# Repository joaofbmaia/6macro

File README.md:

# 6macro
This is my first attempt at designing a keyboard. Is consists of a 6-key board intended for macros or as a dedicated controller for games with few bindings such as OSU.

RGB lighting is supported and the whole build is powered by an ATmega32U2 with the QMK firmware. The 6 switches are PCB-mounted.

The case is still a WIP and is built with stacked layers of laser-cut acrylic and a top layer of decorative aluminum.

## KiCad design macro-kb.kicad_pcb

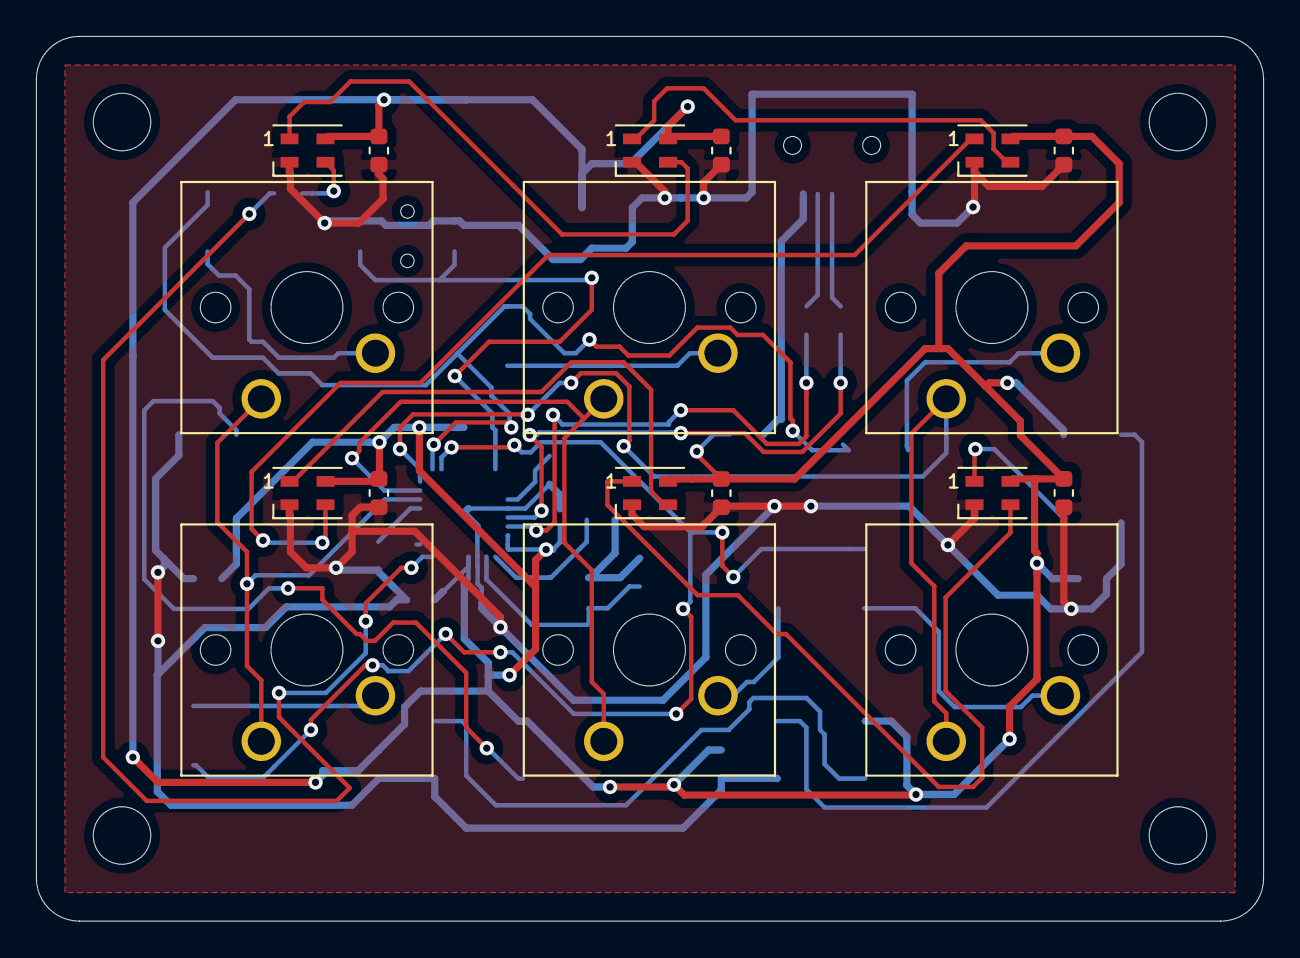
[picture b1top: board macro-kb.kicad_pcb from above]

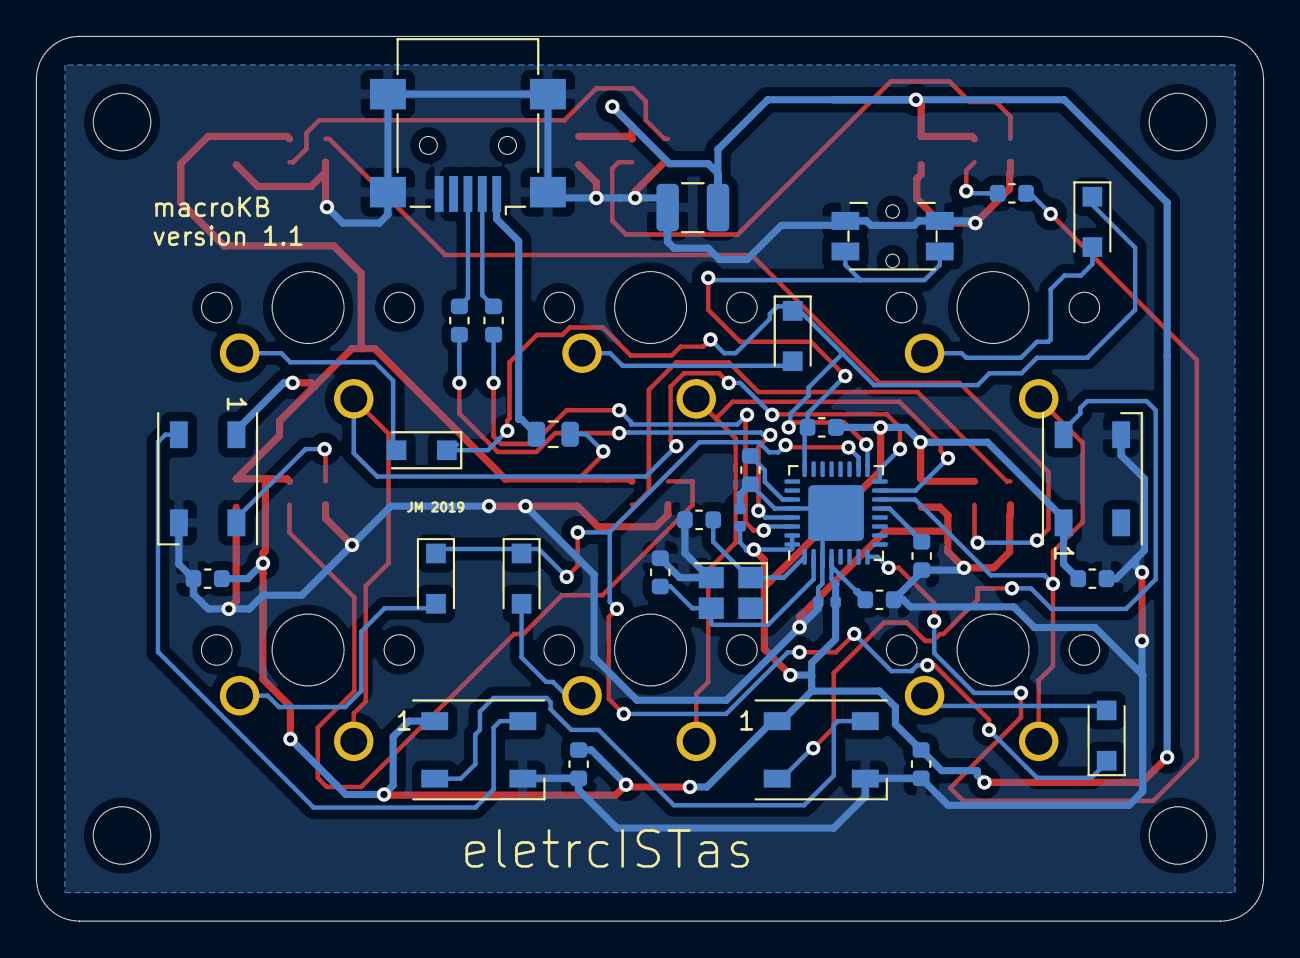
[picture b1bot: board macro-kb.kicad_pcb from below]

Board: 2 copper layers, 68.3 x 49.2 mm, 49 parts (31 on the bottom side), 34 nets.

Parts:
C1: 1uF; C_0603_1608Metric
C2, C3: 0.1uF; C_0402_1005Metric
C4: 10uF; C_0603_1608Metric
C5, C6: 22pF; C_0603_1608Metric
C7, C8, C9, C10, C11, C12, C13, C14, C15, C16: 0.1uF; C_0603_1608Metric
C17: 100uF; C_1210_3225Metric
D1, D2, D3, D4, D5, D6: SOD-123F; D_SOD-123F
D7, D8, D9, D10: WS2812B; LED_WS2812B_PLCC4_5.0x5.0mm_P3.2mm
D11, D12, D13, D14, D15, D16: SK6805; LED_SK6805_PLCC4_2.4x2.7mm_P1.3mm
F1: 500mA; Fuse_0805_2012Metric
MX1, MX2, MX3, MX4, MX5, MX6: MX-1U; SW_Cherry_MX_1.00u_PCB
R1, R4: 10K; R_0603_1608Metric
R2, R3: 22; R_0603_1608Metric
R5: 470; R_0603_1608Metric
SW1: SW_Push; Panasonic_EVQPUL_EVQPUC
U1: ATmega32U2-MU; QFN-32-1EP_5x5mm_P0.5mm_EP3.1x3.1mm
USB1: Mini B; USB_Mini-B_Lumberg_2486_01_Horizontal
Y1: 16MHz 18pF; Crystal_SMD_3225-4Pin_3.2x2.5mm

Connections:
+5V: C2.1, C3.1, C4.1, C7.1, C8.1, C9.1, C10.1, C11.1, C12.1, C13.1, C14.1, C15.1, C16.1, C17.2, D7.1, D8.1, D9.1, D10.1, D11.4, D12.4, D13.4, D14.4, D15.4, D16.4, F1.1, R1.1, U1.4, U1.31, U1.32
COL0: MX1.1, MX4.1, U1.14
COL1: MX2.1, MX5.1, U1.15
COL2: MX3.1, MX6.1, U1.16
D+: R2.2, USB1.3
D-: R3.2, USB1.2
GND: C1.2, C2.2, C3.2, C4.2, C5.2, C6.2, C7.2, C8.2, C9.2, C10.2, C11.2, C12.2, C13.2, C14.2, C15.2, C16.2, C17.1, D7.3, D8.3, D9.3, D10.3, D11.2, D12.2, D13.2, D14.2, D15.2, D16.2, R4.1, SW1.1, U1.3, U1.28, U1.33, USB1.5, USB1.6, Y1.2
KEY_LEDS: R5.2, U1.8
unnamed: C1.1, U1.27
unnamed: C5.1, U1.1, Y1.1
unnamed: C6.1, U1.2, Y1.3
unnamed: D1.2, MX1.2
unnamed: D2.2, MX2.2
unnamed: D3.2, MX3.2
unnamed: D4.2, MX4.2
unnamed: D5.2, MX5.2
unnamed: D6.2, MX6.2
unnamed: D7.2, D8.4
unnamed: D8.2, D9.4
unnamed: D9.2, D10.4
unnamed: D11.1, D12.3
unnamed: D11.3, R5.1
unnamed: D12.1, D13.3
unnamed: D13.1, D14.3
unnamed: D14.1, D15.3
unnamed: D15.1, D16.3
unnamed: R1.2, SW1.2, U1.24
unnamed: R2.1, U1.29
unnamed: R3.1, U1.30
unnamed: R4.2, U1.13
ROW0: D1.1, D2.1, D3.1, U1.17
ROW1: D4.1, D5.1, D6.1, U1.18
UNDERGLOW_LEDS: D7.4, D16.1
VCC: F1.2, USB1.1

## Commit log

2019-05-26 added libs
2019-05-26 basic schematic
2019-05-28 board
2019-05-28 routed
2019-06-08 final version (hopefully)
2019-07-07 new renders
2019-07-07 fixed crossed USB lines v1.1
2019-07-07 new 3d model v1.1
2019-07-18 Photos of the keyboard
2019-07-18 layouts
